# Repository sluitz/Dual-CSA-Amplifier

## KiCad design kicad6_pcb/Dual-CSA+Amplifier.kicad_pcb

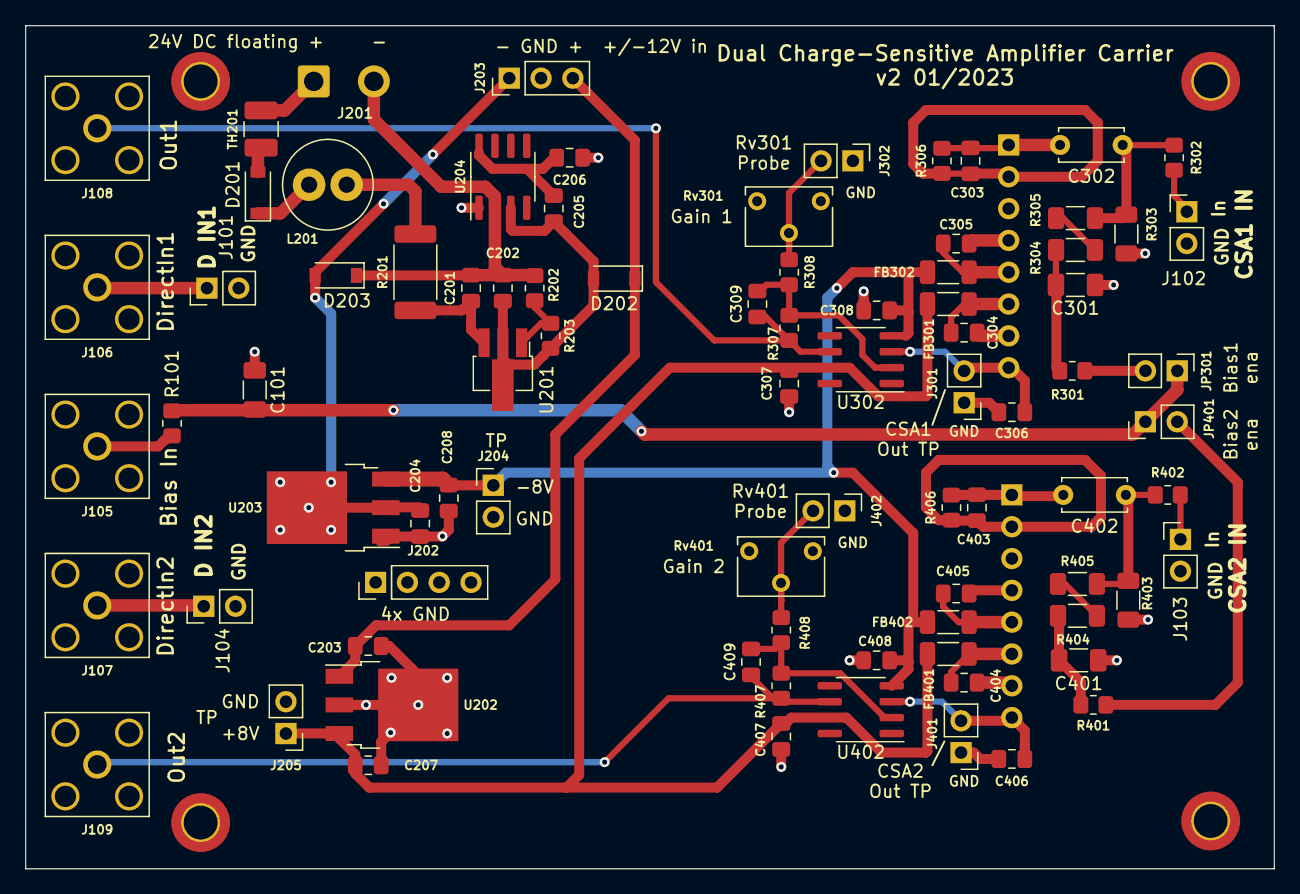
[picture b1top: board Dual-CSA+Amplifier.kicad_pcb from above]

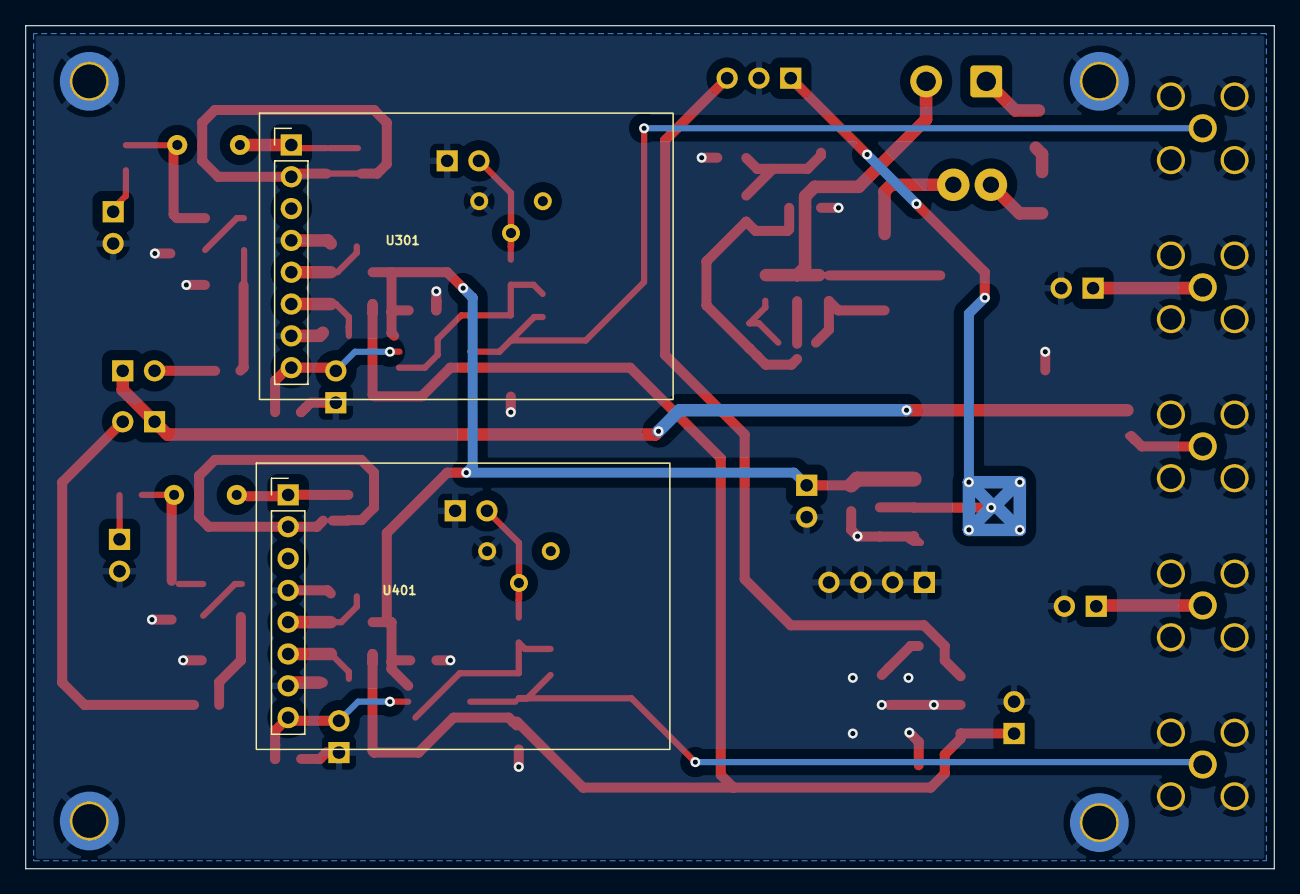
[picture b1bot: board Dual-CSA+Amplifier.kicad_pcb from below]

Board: 2 copper layers, 99.7 x 67.3 mm, 90 parts (2 on the bottom side), 42 nets.

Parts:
C101, C301, C401: 10n; C_1206_3216Metric_Pad1.33x1.80mm_HandSolder
C201, C202: 1uF; C_0805_2012Metric_Pad1.18x1.45mm_HandSolder
C203, C204: 0.33uF; C_0805_2012Metric_Pad1.18x1.45mm_HandSolder
C205, C206, C207, C208, C307, C308, C407, C408: 100nF; C_0805_2012Metric_Pad1.18x1.45mm_HandSolder
C302, C402: 10n; C_Disc_D5.0mm_W2.5mm_P5.00mm
C303, C306, C403, C406: open; C_0805_2012Metric_Pad1.18x1.45mm_HandSolder
C304, C305, C404, C405: 10uF; C_0805_2012Metric_Pad1.18x1.45mm_HandSolder
C309, C409: Open; C_0805_2012Metric_Pad1.18x1.45mm_HandSolder
D201, D202, D203: D; D_SOD-123
FB301, FB302, FB401, FB402: FerriteBead_Small; L_1206_3216Metric_Pad1.22x1.90mm_HandSolder
H101, H102, H103, H104: MountingHole_Pad; MountingHole_2.7mm_M2.5_DIN965_Pad_TopBottom
J101: Direct2 In; PinHeader_1x02_P2.54mm_Vertical
J102: CSA2 In; PinHeader_1x02_P2.54mm_Vertical
J103: CSA1 In; PinHeader_1x02_P2.54mm_Vertical
J104: Direct1 In; PinHeader_1x02_P2.54mm_Vertical
J105: Bias In; SMA_Amphenol_132203-12_Horizontal
J106, J107: Direct in; SMA_Amphenol_132203-12_Horizontal
J108, J109: Output; SMA_Amphenol_132203-12_Horizontal
J201: Barrel_Jack; SolderWire-0.75sqmm_1x02_P4.8mm_D1.25mm_OD2.3mm
J202: GND; PinHeader_1x04_P2.54mm_Vertical
J203: DC Power; PinHeader_1x03_P2.54mm_Vertical
J204: -8V; PinHeader_1x02_P2.54mm_Vertical
J205: +8V; PinHeader_1x02_P2.54mm_Vertical
J301, J401: CA probe; PinHeader_1x02_P2.54mm_Vertical
J302, J402: RV Prob; PinHeader_1x02_P2.54mm_Vertical
JP301, JP401: Jumper_2_Open; PinHeader_1x02_P2.54mm_Vertical
L201: L_Small; L_Radial_D7.0mm_P3.00mm
R101: 1M; R_0805_2012Metric_Pad1.20x1.40mm_HandSolder
R201: 4.7; R_2512_6332Metric_Pad1.40x3.35mm_HandSolder
R202: 7.15k; R_0805_2012Metric_Pad1.20x1.40mm_HandSolder
R203: 430; R_0805_2012Metric_Pad1.20x1.40mm_HandSolder
R301, R401: 10M; R_0805_2012Metric_Pad1.20x1.40mm_HandSolder
R302, R402: 0R; R_0805_2012Metric_Pad1.20x1.40mm_HandSolder
R303, R403: open; R_1206_3216Metric_Pad1.30x1.75mm_HandSolder
R304, R305, R404, R405: 100M; R_1206_3216Metric_Pad1.30x1.75mm_HandSolder
R306, R406: open; R_0805_2012Metric_Pad1.20x1.40mm_HandSolder
R307, R407: 20k; R_0805_2012Metric_Pad1.20x1.40mm_HandSolder
R308, R408: 750; R_0805_2012Metric_Pad1.20x1.40mm_HandSolder
Rv301, Rv401: 10k; Potentiometer_Bourns_3266W_Vertical
TH201: PTC 200mA; Fuse_1210_3225Metric_Pad1.42x2.65mm_HandSolder
U201: LM317L; SOT-89-3_Handsoldering
U202: UA78M08; TO-252-3_TabPin2
U203: UA79M08; TO-252-3_TabPin2
U204: TLE2426xP; SOIC-8_3.9x4.9mm_P1.27mm
U301, U401: CR110; CR11x
U302, U402: TL071; SOIC-8_3.9x4.9mm_P1.27mm

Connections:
+8V: C207.1, C307.1, C407.1, FB301.2, FB401.2, J205.1, U202.3 (OUT), U302.7 (V+), U402.7 (V+)
-8V: C208.1, C308.1, C408.1, FB302.2, FB402.2, J204.1, U203.3 (VO), U302.4 (V-), U402.4 (V-)
/CSA+Amp1/CSA_IN: J103.1, R402.2
/CSA+Amp1/Out: C409.1, J109.1 (In), R407.2, U402.6
/CSA+Amp/BIAS_IN: C101.2, JP301.1 (A), JP401.1 (A), R101.1
/CSA+Amp/CSA_IN: J102.1, R302.2
/CSA+Amp/Out: C309.1, J108.1 (In), R307.2, U302.6
GND: C101.1, C203.2, C204.2, C206.2, C207.2, C208.2, C301.1, C303.1, C304.2, C305.2, C306.2, C307.2, C308.2, C401.1, C403.1, C404.2, C405.2, C406.2, C407.2, C408.2, H101.1, H102.1, H103.1, H104.1, J101.2, J102.2, J103.2, J104.2, J105.2 (Ext), J106.2 (Ext), J107.2 (Ext), J108.2 (Ext), J109.2 (Ext), J202.1, J202.2, J202.3, J202.4, J203.2, J204.2, J205.2, J301.1, J302.1, J401.1, J402.1, R303.1, R306.1, R403.1, R406.1, Rv301.1, Rv401.1, U202.2 (GND), U203.1 (GND), U204.1 (OUT), U301.2 (GND), U301.4 (GND), U301.7 (GND), U401.2 (GND), U401.4 (GND), U401.7 (GND)
unnamed: C201.1, R201.1, U201.3 (VI)
unnamed: C201.2, C202.2, D203.1 (K), J201.2, R202.2, U204.2 (COMMON)
unnamed: C202.1, C205.1, D202.2 (A), R203.1, U201.2 (VO), U204.3 (IN)
unnamed: C203.1, D202.1 (K), J203.3, U202.1 (IN)
unnamed: C204.1, D203.2 (A), J203.1, U203.2 (VI)
unnamed: C205.2, C206.1, U204.8 (NOISE_REDUCTION)
unnamed: C301.2, R301.1, R304.1
unnamed: C302.1, R302.1, R303.2, R305.2
unnamed: C302.2, C303.2, R306.2, U301.1 (Input)
unnamed: C304.1, FB301.1, U301.6 (+Vs)
unnamed: C305.1, FB302.1, U301.5 (-Vs)
unnamed: C306.1, J301.2, U301.8 (output), U302.3 (+)
unnamed: C309.2, R307.1, R308.2, U302.2 (-)
unnamed: C401.2, R401.1, R404.1
unnamed: C402.1, R402.1, R403.2, R405.2
unnamed: C402.2, C403.2, R406.2, U401.1 (Input)
unnamed: C404.1, FB401.1, U401.6 (+Vs)
unnamed: C405.1, FB402.1, U401.5 (-Vs)
unnamed: C406.1, J401.2, U401.8 (output), U402.3 (+)
unnamed: C409.2, R407.1, R408.2, U402.2 (-)
unnamed: D201.1 (K), L201.1
unnamed: D201.2 (A), TH201.1
unnamed: J101.1, J106.1 (In)
unnamed: J104.1, J107.1 (In)
unnamed: J105.1 (In), R101.2
unnamed: J201.1, TH201.2
unnamed: J302.2, R308.1, Rv301.2
unnamed: J402.2, R408.1, Rv401.2
unnamed: JP301.2 (B), R301.2
unnamed: JP401.2 (B), R401.2
unnamed: L201.2, R201.2
unnamed: R202.1, R203.2, U201.1 (ADJ)
unnamed: R304.2, R305.1
unnamed: R404.2, R405.1

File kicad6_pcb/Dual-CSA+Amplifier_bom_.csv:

Component,Description,Part,References,Value,Footprint,Quantity Per PCB,Datasheet,Mouser,Digikey
1,Unpolarized capacitor,C,C101 C301 C401,10n,C_1206_3216Metric_Pad1.33x1.80mm_HandSolder,3,https://www.mouser.com/datasheet/2/212/KEM_C1007_X8R_ULTRA_1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,80-C1206C104K3HAUTO,
2,Unpolarized capacitor,C,C302 C402,10n,C_Disc_D5.0mm_W2.5mm_P5.00mm,2,https://product.tdk.com/system/files/dam/doc/product/capacit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,810-FA26C0G2J103JNU6,
3,"Unpolarized capacitor, small symbol",C_Small,C205 C206 C207 C208 C307 C308 C407 C408,100nF,C_0805_2012Metric_Pad1.18x1.45mm_HandSolder,8,https://www.mouser.com/ProductDetail/KEMET/C0805C104K5RAC741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,80-C0805C104K5RACLR,
4,"Unpolarized capacitor, small symbol",C_Small,C203 C204,0.33uF,C_0805_2012Metric_Pad1.18x1.45mm_HandSolder,2,https://www.mouser.com/datasheet/2/212/1/KEM_C1078_X7R_FT_CA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,80-C0805X334K5RAUTO,
5,"Unpolarized capacitor, small symbol",C_Small,C201 C202,1uF,C_0805_2012Metric_Pad1.18x1.45mm_HandSolder,2,https://product.tdk.com/system/files/dam/doc/product/capacit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,810-C2012X7R1H105K,
6,"Unpolarized capacitor, small symbol",C_Small,C304 C305 C404 C405,10uF,C_0805_2012Metric_Pad1.18x1.45mm_HandSolder,4,https://www.mouser.com/datasheet/2/396/mlcc02_e-1307760.pdf,963-GMK212BBJ106KG-T,
7,"Unpolarized capacitor, small symbol",C_Small,C303 C306 C309 C403 C406 C409,open,C_0805_2012Metric_Pad1.18x1.45mm_HandSolder,6,~,80-C0805C104K5RACLR,
8,Schottky diode,D_Schottky_1,D201 D202,D,D_SOD-123,2,https://fscdn.rohm.com/en/products/databook/datasheet/discre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,755-RBR2L40ADDTE25,
9,Schottky diode,D_Schottky,D203,D,D_SOD-123,1,https://fscdn.rohm.com/en/products/databook/datasheet/discre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,755-RBR2L40ADDTE25,
10,"Ferrite bead, small symbol",FerriteBead_Small,FB301 FB302 FB401 FB402,FerriteBead_Small,L_1206_3216Metric_Pad1.22x1.90mm_HandSolder,4,https://www.mouser.com/datasheet/2/54/Bourns_MGMUMZ_datashee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,652-MU3261-301Y,732-6715-1-ND
11,DC Barrel Jack,Barrel_Jack,J201,Barrel_Jack,SolderWire-0.75sqmm_1x02_P4.8mm_D1.25mm_OD2.3mm,1,https://www.digikey.com/en/products/detail/tensility-interna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,,839-1580-ND
12,"coaxial connector (BNC, SMA, SMB, SMC, Cinch/RCA, LEMO, ...)",Conn_Coaxial,J105 J106 J107 J108 J109,Bias In,SMA_Amphenol_132203-12_Horizontal,5,https://www.mouser.com/datasheet/2/238/consma002-l-g-1544715.pdf,712-CONSMA002-L-G,
13,"Generic connector, single row, 01x02, script generated (kicad-library-utils/schlib/autogen/connector/)",Conn_01x02_Male,J301 J302 J401 J402,CA probe,PinHeader_1x02_P2.54mm_Vertical,4,~,,
14,"Generic connector, single row, 01x03, script generated (kicad-library-utils/schlib/autogen/connector/)",Conn_01x03,J203,DC Power,PinHeader_1x03_P2.54mm_Vertical,1,~,,
15,"Generic connector, single row, 01x02, script generated (kicad-library-utils/schlib/autogen/connector/)",Conn_01x02,J101 J102 J103 J104 J204 J205,Direct2 In,PinHeader_1x02_P2.54mm_Vertical,6,~,,
16,"Generic connector, single row, 01x04, script generated (kicad-library-utils/schlib/autogen/connector/)",Conn_01x04_Male,J202,GND,PinHeader_1x04_P2.54mm_Vertical,1,~,,
17,"Jumper, 2-pole, open",Jumper_2_Open,JP301 JP401,Jumper_2_Open,PinHeader_1x02_P2.54mm_Vertical,2,~,,
18,"Inductor, small symbol",L_Small,L201,L_Small,L_Radial_D7.0mm_P3.00mm,1,https://www.mouser.com/datasheet/2/54/rlb-777833.pdf,652-RLB0812-101KL,RLB0812-101KL-ND
19,"Resistor, small symbol",R_Small,R302 R402,0R,R_0805_2012Metric_Pad1.20x1.40mm_HandSolder,2,https://www.mouser.com/datasheet/2/427/crcwhpe3-1713858.pdf,71-CRCW08050000Z0EAH,
20,"Resistor, small US symbol",R_Small_US,R201,4.7,R_2512_6332Metric_Pad1.40x3.35mm_HandSolder,1,https://www.mouser.com/datasheet/2/418/5/ENG_DS_9_1773463_7_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,667-ERJ-P06F4300V,A121265CT-ND
21,"Resistor, small US symbol",R_Small_US,R203,430,R_0805_2012Metric_Pad1.20x1.40mm_HandSolder,1,https://www.mouser.com/datasheet/2/315/AOA0000C331-1141874.pdf,667-ERJ-P06F4300V,
22,"Resistor, small symbol",R_Small,R308 R408,750,R_0805_2012Metric_Pad1.20x1.40mm_HandSolder,2,~,71-CRCW0805750RFKEAC,
23,"Resistor, small US symbol",R_Small_US,R202,7.15k,R_0805_2012Metric_Pad1.20x1.40mm_HandSolder,1,https://www.mouser.com/datasheet/2/348/ROHM_S_A0011075115_1-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,755-KTR10EZPF7151,311-2.94KCRCT-ND
24,"Resistor, small symbol",R_Small,R307 R407,20k,R_0805_2012Metric_Pad1.20x1.40mm_HandSolder,2,~,667-ERJ-6ENF2002V,
25,"Resistor, small symbol",R_Small,R101,1M,R_0805_2012Metric_Pad1.20x1.40mm_HandSolder,1,https://www.mouser.com/datasheet/2/315/AOA0000C334-1314047.pdf,667-ERJ-S06F1005V,
26,"Resistor, small symbol",R_Small,R301 R401,10M,R_0805_2012Metric_Pad1.20x1.40mm_HandSolder,2,https://www.mouser.com/datasheet/2/315/AOA0000C334-1314047.pdf,667-ERJ-S06F1005V,
27,"Resistor, small symbol",R_Small,R304 R305 R404 R405,100M,R_1206_3216Metric_Pad1.30x1.75mm_HandSolder,4,https://www.mouser.com/datasheet/2/427/dcrcwhre3-1761765.pdf,71-CRCW1206100MJPEAR,
28,"Resistor, small symbol",R_Small,R303 R403,open,R_1206_3216Metric_Pad1.30x1.75mm_HandSolder,2,~,,
29,"Resistor, small symbol",R_Small,R306 R406,open,R_0805_2012Metric_Pad1.20x1.40mm_HandSolder,2,~,,
30,Trim-potentiometer,R_Potentiometer_Trim,Rv301 Rv401,10k,Potentiometer_Bourns_3266W_Vertical,2,~,652-3266W-1-103LF,
31,"Temperature dependent resistor, positive temperature coefficient, US symbol",Thermistor_PTC_US,TH201,PTC 200mA,Fuse_1210_3225Metric_Pad1.42x2.65mm_HandSolder,1,https://www.mouser.com/datasheet/2/643/ds_CP_0zch_series-166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,530-0ZCH0020FF2E,
32,,CR110,U301 U401,CR110,CR11x,2,,575-8019300810012000,
33,"1.5A 35V Adjustable Linear Regulator, TO-220",LM317_TO-220,U201,LM317L,SOT-89-3_Handsoldering,1,https://www.ti.com/general/docs/suppproductinfo.tsp?distId=2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,595-LM317LCPK,296-50352-1-ND
34,"Single Low-Noise JFET-Input Operational Amplifiers, DIP-8/SOIC-8",TL071,U302 U402,TL071,SOIC-8_3.9x4.9mm_P1.27mm,2,http://www.ti.com/lit/ds/symlink/tl071.pdf,595-TL071CDR,
35,"Precision virtual ground, noise reduction pin, 4V to 40V input, SOIC-8",TLE2426xD,U204,TLE2426xP,SOIC-8_3.9x4.9mm_P1.27mm,1,https://www.mouser.com/c/semiconductors/power-management-ics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,595-TLE2426MD,296-47278-1-ND
36,"Positive 1A 35V Linear Regulator, Fixed Output 8V, TO-220/TO-263",uA7808,U202,UA78M08,TO-252-3_TabPin2,1,https://www.ti.com/general/docs/suppproductinfo.tsp?distId=2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,595-UA78M08CKVURG3,296-12612-1-ND
37,"Negative 1A 35V Linear Regulator, Fixed Output 8V, TO-220",LM7908_TO220,U203,UA79M08,TO-252-3_TabPin2,1,https://www.onsemi.com/pub/Collateral/MC7900-D.PDF,595-UA79M08CKVURG3,296-19678-1-ND





Component Groups:,37
Component Count:,86
Fitted Components:,86
Number of PCBs:,1
Total components:,86
Schematic Version:,
Schematic Date:,
PCB Variant:,default
BoM Date:,1/13/2023 3:21:15 PM
Schematic Source:,Dual-CSA+Amplifier.kicad_sch
KiCad Version:,Eeschema (6.0.9)

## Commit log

2023-10-12 Additional saves.
2023-10-12 Update to KiCad 7. Added some freecad parts (unfortunately, thoroughly broken).
2023-10-12 CSA carrier v2. Multiple fixes and improvements.
